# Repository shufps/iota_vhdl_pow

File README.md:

# IOTA VHDL PoW (Pearl Diver)

Project moved to:

https://gitlab.com/microengineer18/pidiver1.3/wikis/home

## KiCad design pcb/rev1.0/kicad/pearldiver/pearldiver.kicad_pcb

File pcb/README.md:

Files not suitable for machine assembly!
Board files are outdated ... New files with many improvements coming #soon

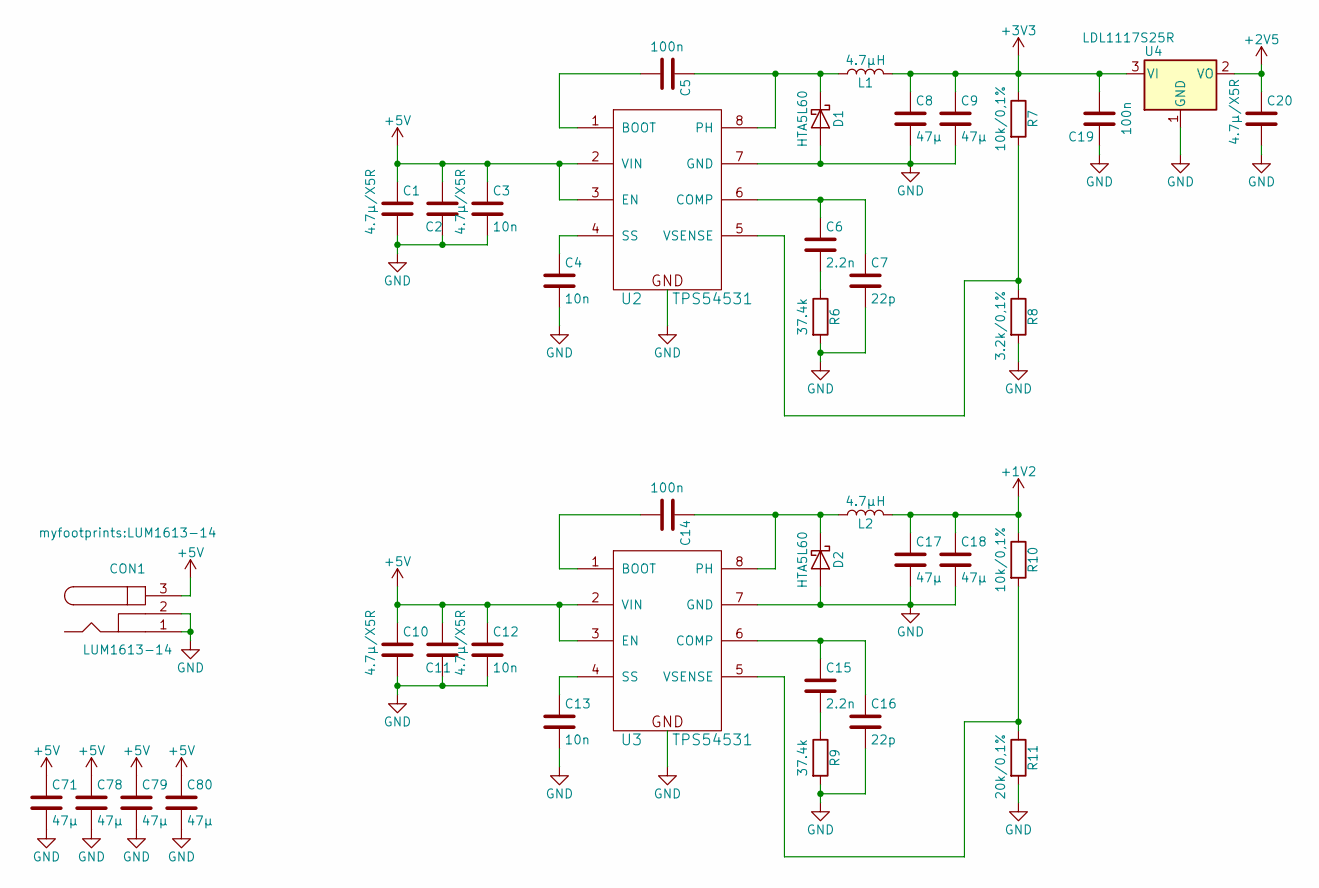
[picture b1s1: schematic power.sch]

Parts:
C1, C2, C10, C11, C20: 4.7µ/X5R; C_1206
C3, C4, C12, C13: 10n; C_0805
C5, C14: 100n; C_0805
C6, C15: 2.2n; C_0805
C7, C16: 22p; C_0603
C8, C9, C17, C18, C71, C78, C79, C80: 47µ; C_1210
C19: 100n; C_1206
CON1: LUM1613-14
D1, D2: HTA5L60; D_SMA
L1, L2: 4.7µH; IHLP-3232DZ-01
R6, R9: 37.4k; R_1206
R7, R10: 10k/0,1%; R_1206
R8: 3.2k/0,1%; R_1206
R11: 20k/0,1%; R_1206
U2, U3: TPS54531; SOIC-8-1EP_3.9x4.9mm_Pitch1.27mm
U4: LDL1117S25R; SOT-223-3_TabPin2

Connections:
+1V2: C17.1, C18.1, L2.2, R10.1; also elsewhere on the board
+2V5: C20.1, U4.2 (VO); also elsewhere on the board
+5V: C1.1, C2.1, C3.1, C10.1, C11.1, C12.1, C71.1, C78.1, C79.1, C80.1, CON1.3, U2.2 (VIN), U2.3 (EN), U3.2 (VIN), U3.3 (EN); also elsewhere on the board
GND: C1.2, C2.2, C3.2, C4.2, C7.2, C8.2, C9.2, C10.2, C11.2, C12.2, C13.2, C16.2, C17.2, C18.2, C19.1, C20.2, C71.2, C78.2, C79.2, C80.2, CON1.1, CON1.2, D1.2 (A), D2.2 (A), R6.2, R8.2, R9.2, R11.2, U2.7 (GND), U2.9 (GND), U3.7 (GND), U3.9 (GND), U4.1 (GND); also elsewhere on the board
unnamed: C4.1, U2.4 (SS)
unnamed: C5.1, D1.1 (K), L1.1, U2.8 (PH)
unnamed: C5.2, U2.1 (BOOT)
unnamed: C6.1, C7.1, U2.6 (COMP)
unnamed: C6.2, R6.1
unnamed: C13.1, U3.4 (SS)
unnamed: C14.1, D2.1 (K), L2.1, U3.8 (PH)
unnamed: C14.2, U3.1 (BOOT)
unnamed: C15.1, C16.1, U3.6 (COMP)
unnamed: C15.2, R9.1
unnamed: R7.2, R8.1, U2.5 (VSENSE)
unnamed: R10.2, R11.1, U3.5 (VSENSE)

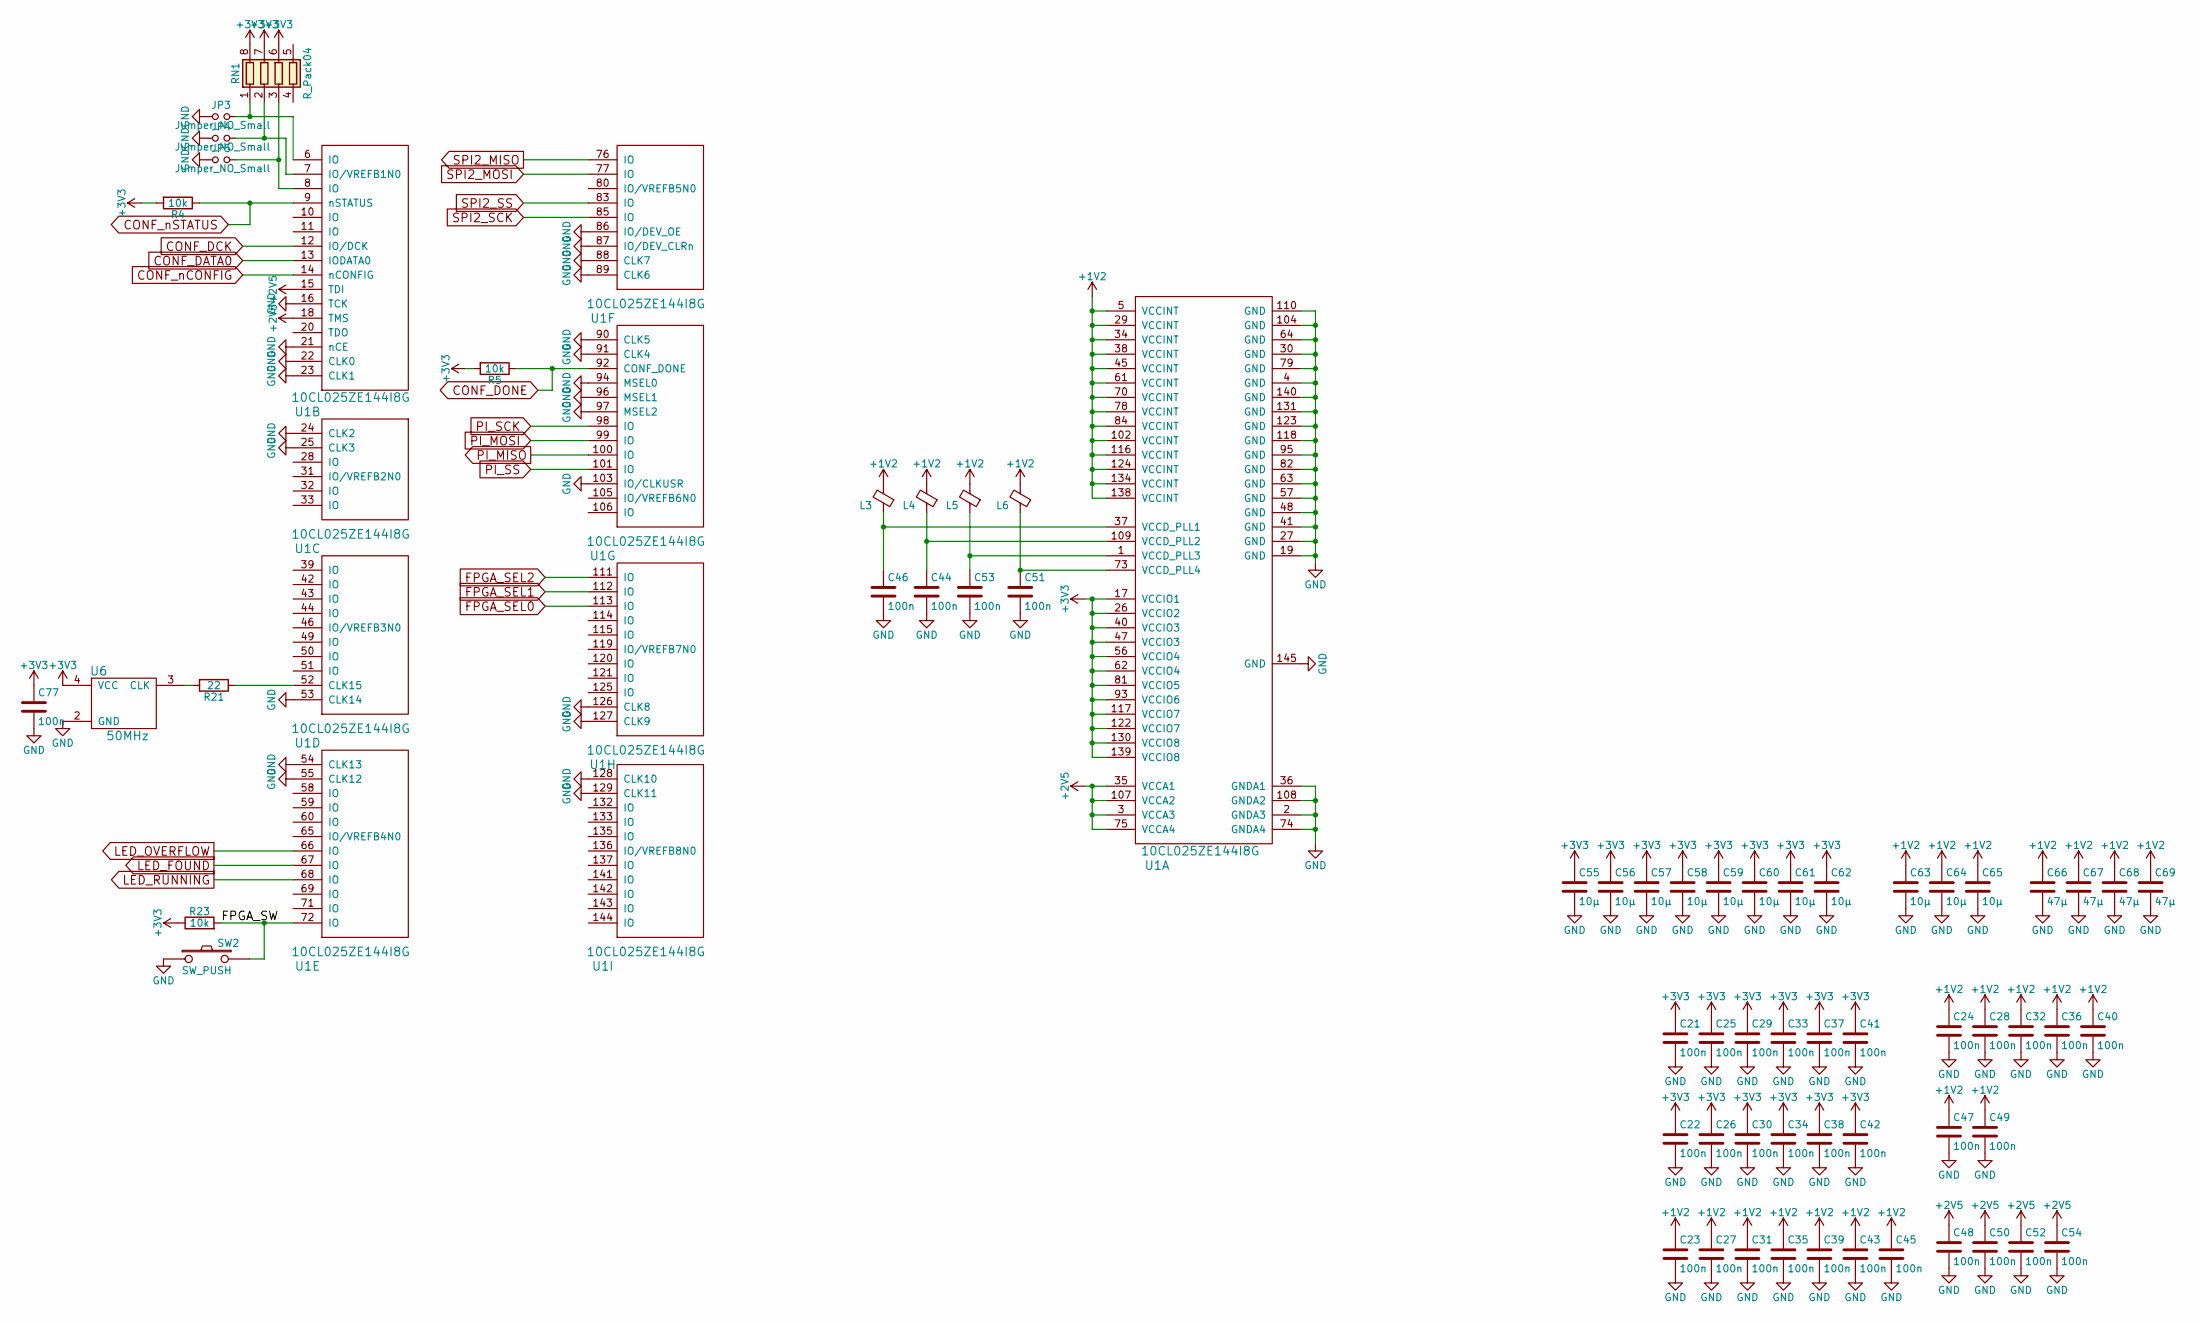
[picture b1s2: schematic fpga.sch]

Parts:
C21, C22, C23, C24, C25, C26, C27, C28, C29, C30, C31, C32, C33, C34, C35, C36, C37, C38, C39, C40, C41, C42, C43, C44, C45, C46, C47, C48, C49, C50, C51, C52, C53, C54: 100n; C_0603
C55, C56, C57, C58, C59, C60, C61, C62, C63, C64, C65: 10µ; C_1206
C66, C67, C68, C69: 47µ; C_1206
C77: 100n; C_0805
JP3, JP4, JP5: Jumper_NO_Small; SOLDERJMP
L3, L4, L5, L6: Ferrite_Bead_Small; R_0805
R4, R5, R23: 10k; R_0805
R21: 22; C_0805
RN1: R_Pack04; R_Array_Convex_4x0603
SW2: SW_PUSH; KURZHUB_SMD
U1: 10CL025ZE144I8G; EQFP-144_20x20mm_Pitch0.5mm
U6: 50MHz; Oscillator_SMD_EuroQuartz_XO32-4pin_3.2x2.5mm_HandSoldering

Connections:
+1V2: C23.1, C24.1, C27.1, C28.1, C31.1, C32.1, C35.1, C36.1, C39.1, C40.1, C43.1, C45.1, C47.1, C49.1, C63.1, C64.1, C65.1, C66.1, C67.1, C68.1, C69.1, L3.2, L4.2, L5.2, L6.2, U1.5 (VCCINT), U1.29 (VCCINT), U1.34 (VCCINT), U1.38 (VCCINT), U1.45 (VCCINT), U1.61 (VCCINT), U1.70 (VCCINT), U1.78 (VCCINT), U1.84 (VCCINT), U1.102 (VCCINT), U1.116 (VCCINT), U1.124 (VCCINT), U1.134 (VCCINT), U1.138 (VCCINT); also elsewhere on the board
+2V5: C48.1, C50.1, C52.1, C54.1, U1.3 (VCCA3), U1.15 (TDI), U1.18 (TMS), U1.35 (VCCA1), U1.75 (VCCA4), U1.107 (VCCA2); also elsewhere on the board
/fpga/FPGA_SW: R23.2, SW2.2, U1.72 (IO)
CONF_DATA0: U1.13 (IODATA0); also elsewhere on the board
CONF_DCK: U1.12 (IO/DCK); also elsewhere on the board
CONF_DONE: R5.1, U1.92 (CONF_DONE); also elsewhere on the board
CONF_nCONFIG: U1.14 (nCONFIG); also elsewhere on the board
CONF_nSTATUS: R4.1, U1.9 (nSTATUS); also elsewhere on the board
FPGA_SEL0: U1.113 (IO); also elsewhere on the board
FPGA_SEL1: U1.112 (IO); also elsewhere on the board
FPGA_SEL2: U1.111 (IO); also elsewhere on the board
GND: C21.2, C22.2, C23.2, C24.2, C25.2, C26.2, C27.2, C28.2, C29.2, C30.2, C31.2, C32.2, C33.2, C34.2, C35.2, C36.2, C37.2, C38.2, C39.2, C40.2, C41.2, C42.2, C43.2, C44.2, C45.2, C46.2, C47.2, C48.2, C49.2, C50.2, C51.2, C52.2, C53.2, C54.2, C55.2, C56.2, C57.2, C58.2, C59.2, C60.2, C61.2, C62.2, C63.2, C64.2, C65.2, C66.2, C67.2, C68.2, C69.2, C77.2, JP3.1, JP4.1, JP5.1, SW2.1, U1.2 (GNDA3), U1.4 (GND), U1.16 (TCK), U1.19 (GND), U1.21 (nCE), U1.22 (CLK0), U1.23 (CLK1), U1.24 (CLK2), U1.25 (CLK3), U1.27 (GND), U1.30 (GND), U1.36 (GNDA1), U1.41 (GND), U1.48 (GND), U1.53 (CLK14), U1.54 (CLK13), U1.55 (CLK12), U1.57 (GND), U1.63 (GND), U1.64 (GND), U1.74 (GNDA4), U1.79 (GND), U1.82 (GND), U1.86 (IO/DEV_OE), U1.87 (IO/DEV_CLRn), U1.88 (CLK7), U1.89 (CLK6), U1.90 (CLK5), U1.91 (CLK4), U1.94 (MSEL0), U1.95 (GND), U1.96 (MSEL1), U1.97 (MSEL2), U1.103 (IO/CLKUSR), U1.104 (GND), U1.108 (GNDA2), U1.110 (GND), U1.118 (GND), U1.123 (GND), U1.126 (CLK8), U1.127 (CLK9), U1.128 (CLK10), U1.129 (CLK11), U1.131 (GND), U1.140 (GND), U1.145 (GND), U6.2 (GND); also elsewhere on the board
LED_FOUND: U1.67 (IO); also elsewhere on the board
LED_OVERFLOW: U1.66 (IO); also elsewhere on the board
LED_RUNNING: U1.68 (IO); also elsewhere on the board
unnamed: C44.1, L4.1, U1.109 (VCCD_PLL2)
unnamed: C46.1, L3.1, U1.37 (VCCD_PLL1)
unnamed: C51.1, L6.1, U1.73 (VCCD_PLL4)
unnamed: C53.1, L5.1, U1.1 (VCCD_PLL3)
unnamed: JP3.2, RN1.1 (R1.1), U1.6 (IO)
unnamed: JP4.2, RN1.2 (R2.1), U1.7 (IO/VREFB1N0)
unnamed: JP5.2, RN1.3 (R3.1), U1.8 (IO)
unnamed: R21.1, U1.52 (CLK15)
unnamed: R21.2, U6.3 (CLK)
PI_MISO: U1.100 (IO); also elsewhere on the board
PI_MOSI: U1.99 (IO); also elsewhere on the board
PI_SCK: U1.98 (IO); also elsewhere on the board
PI_SS: U1.101 (IO); also elsewhere on the board
SPI2_MISO: U1.76 (IO); also elsewhere on the board
SPI2_MOSI: U1.77 (IO); also elsewhere on the board
SPI2_SCK: U1.85 (IO); also elsewhere on the board
SPI2_SS: U1.83 (IO); also elsewhere on the board

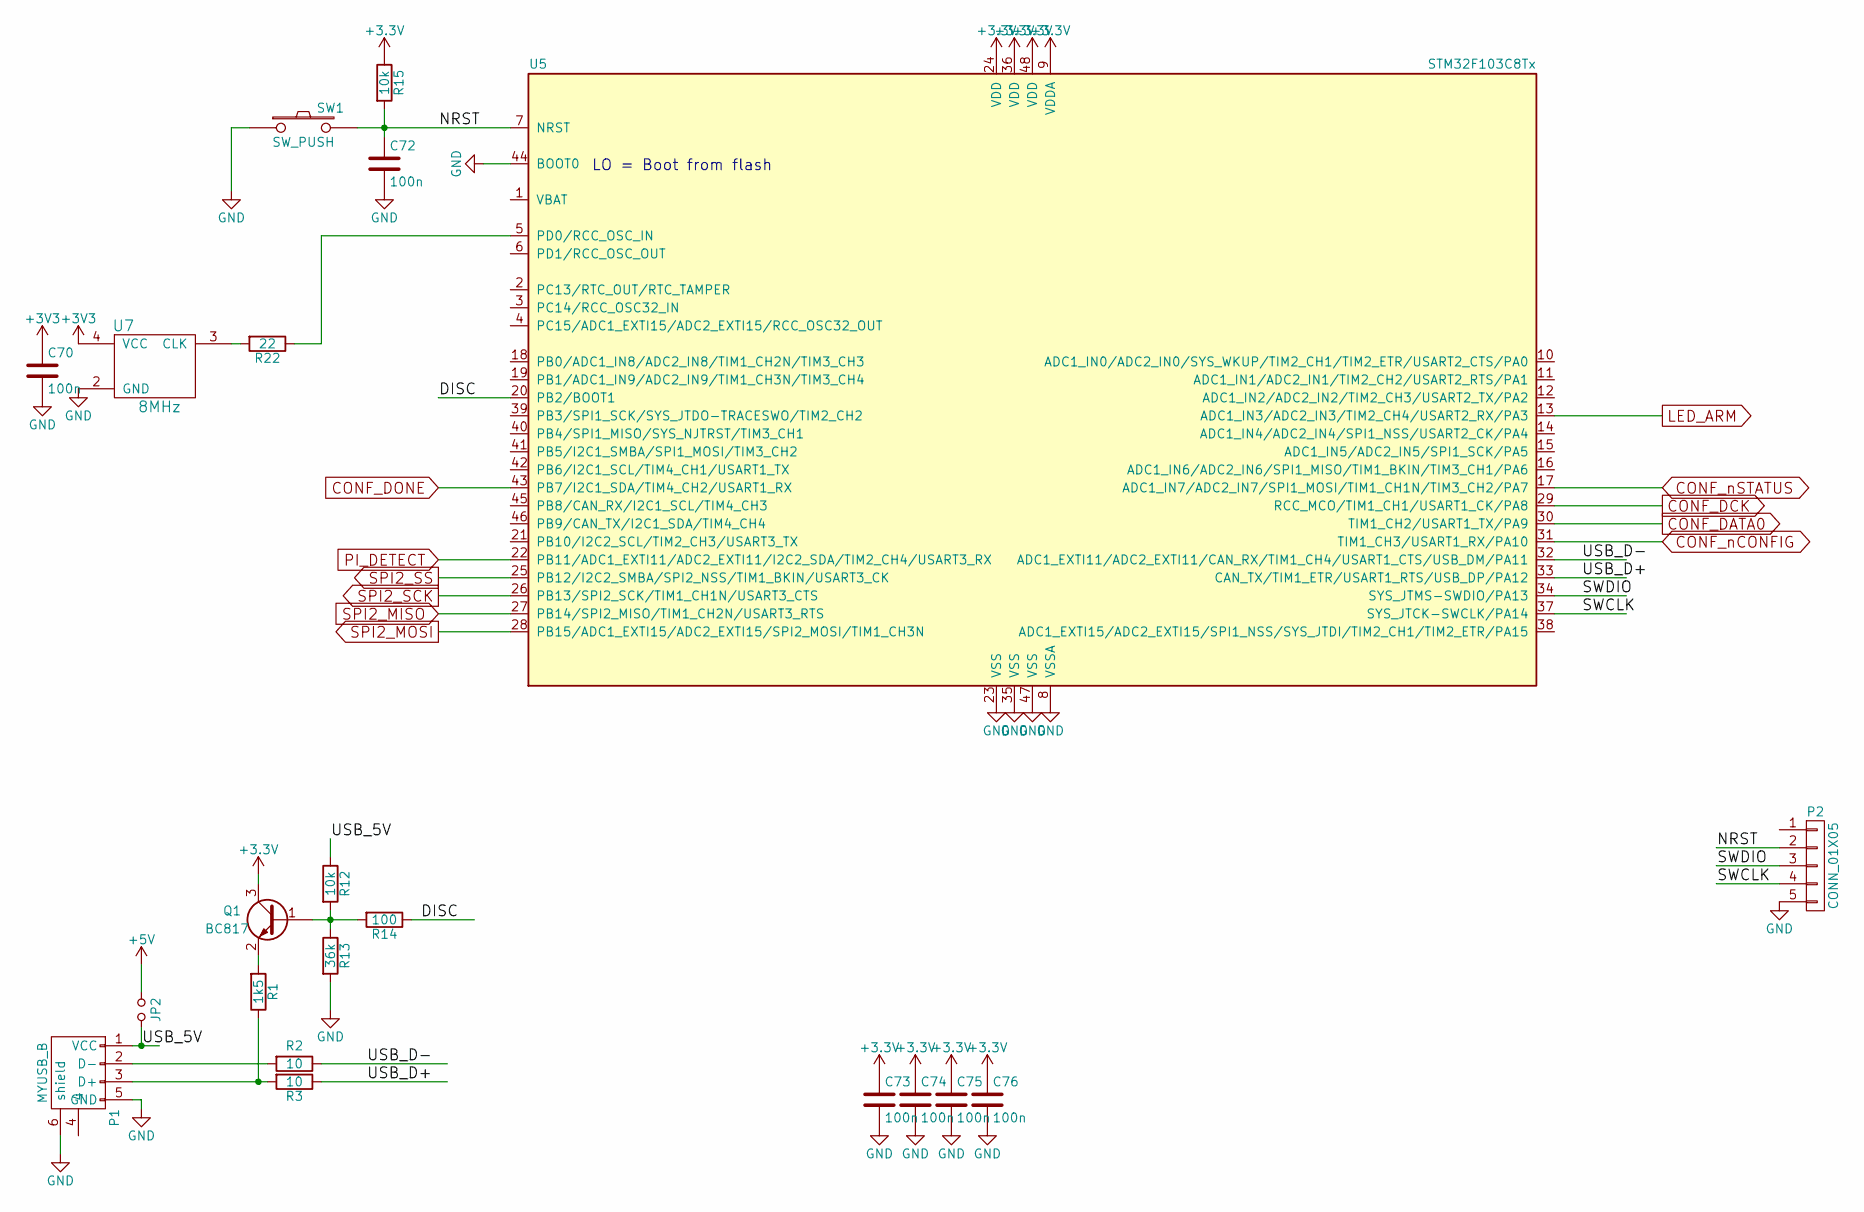
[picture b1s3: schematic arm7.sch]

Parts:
C70, C72, C73, C74, C75, C76: 100n; C_0805
JP2: Jumper_NO_Small; SOLDERJMP
P1: MYUSB_B; MICROUSBB
P2: CONN_01X05; Pin_Header_Straight_1x05_Pitch1.27mm
Q1: BC817; SOT-23
R1: 1k5; R_0805
R2, R3: 10; R_0805
R12, R15: 10k; R_0805
R13: 36k; R_0805
R14: 100; R_0805
R22: 22; C_0805
SW1: SW_PUSH; KURZHUB_SMD
U5: STM32F103C8Tx; LQFP-48_7x7mm_Pitch0.5mm
U7: 8MHz; Oscillator_SMD_EuroQuartz_XO32-4pin_3.2x2.5mm_HandSoldering

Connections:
+5V: JP2.1; also elsewhere on the board
/arm7/DISC: R14.1, U5.20 (PB2/BOOT1)
/arm7/NRST: C72.1, P2.2, R15.2, SW1.2, U5.7 (NRST)
/arm7/SWCLK: P2.4, U5.37 (SYS_JTCK-SWCLK/PA14)
/arm7/SWDIO: P2.3, U5.34 (SYS_JTMS-SWDIO/PA13)
/arm7/USB_5V: JP2.2, P1.1 (VCC), R12.1
/arm7/USB_D+: R3.1, U5.33 (CAN_TX/TIM1_ETR/USART1_RTS/USB_DP/PA12)
/arm7/USB_D-: R2.1, U5.32 (ADC1_EXTI11/ADC2_EXTI11/CAN_RX/TIM1_CH4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)
CONF_DATA0: U5.30 (TIM1_CH2/USART1_TX/PA9); also elsewhere on the board
CONF_DCK: U5.29 (RCC_MCO/TIM1_CH1/USART1_CK/PA8); also elsewhere on the board
CONF_DONE: U5.43 (PB7/I2C1_SDA/TIM4_CH2/USART1_RX); also elsewhere on the board
CONF_nCONFIG: U5.31 (TIM1_CH3/USART1_RX/PA10); also elsewhere on the board
CONF_nSTATUS: U5.17 (ADC1_IN7/ADC2_IN7/SPI1_MOSI/TIM1_CH1N/T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); also elsewhere on the board
GND: C70.2, C72.2, C73.2, C74.2, C75.2, C76.2, P1.5 (GND), P1.6 (shield), P2.5, R13.2, SW1.1, U5.8 (VSSA), U5.23 (VSS), U5.35 (VSS), U5.44 (BOOT0), U5.47 (VSS), U7.2 (GND); also elsewhere on the board
LED_ARM: U5.13 (ADC1_IN3/ADC2_IN3/TIM2_CH4/USART2_RX/PA3); also elsewhere on the board
unnamed: P1.2 (D-), R2.2
unnamed: P1.3 (D+), R1.1, R3.2
unnamed: Q1.1 (B), R12.2, R13.1, R14.2
unnamed: Q1.2 (E), R1.2
unnamed: R22.1, U5.5 (PD0/RCC_OSC_IN)
unnamed: R22.2, U7.3 (CLK)
PI_DETECT: U5.22 (PB11/ADC1_EXTI11/ADC2_EXTI11/I2C2_SDA/T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); also elsewhere on the board
SPI2_MISO: U5.27 (PB14/SPI2_MISO/TIM1_CH2N/USART3_RTS); also elsewhere on the board
SPI2_MOSI: U5.28 (PB15/ADC1_EXTI15/ADC2_EXTI15/SPI2_MOSI/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); also elsewhere on the board
SPI2_SCK: U5.26 (PB13/SPI2_SCK/TIM1_CH1N/USART3_CTS); also elsewhere on the board
SPI2_SS: U5.25 (PB12/I2C2_SMBA/SPI2_NSS/TIM1_BKIN/USART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); also elsewhere on the board

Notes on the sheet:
LO = Boot from flash

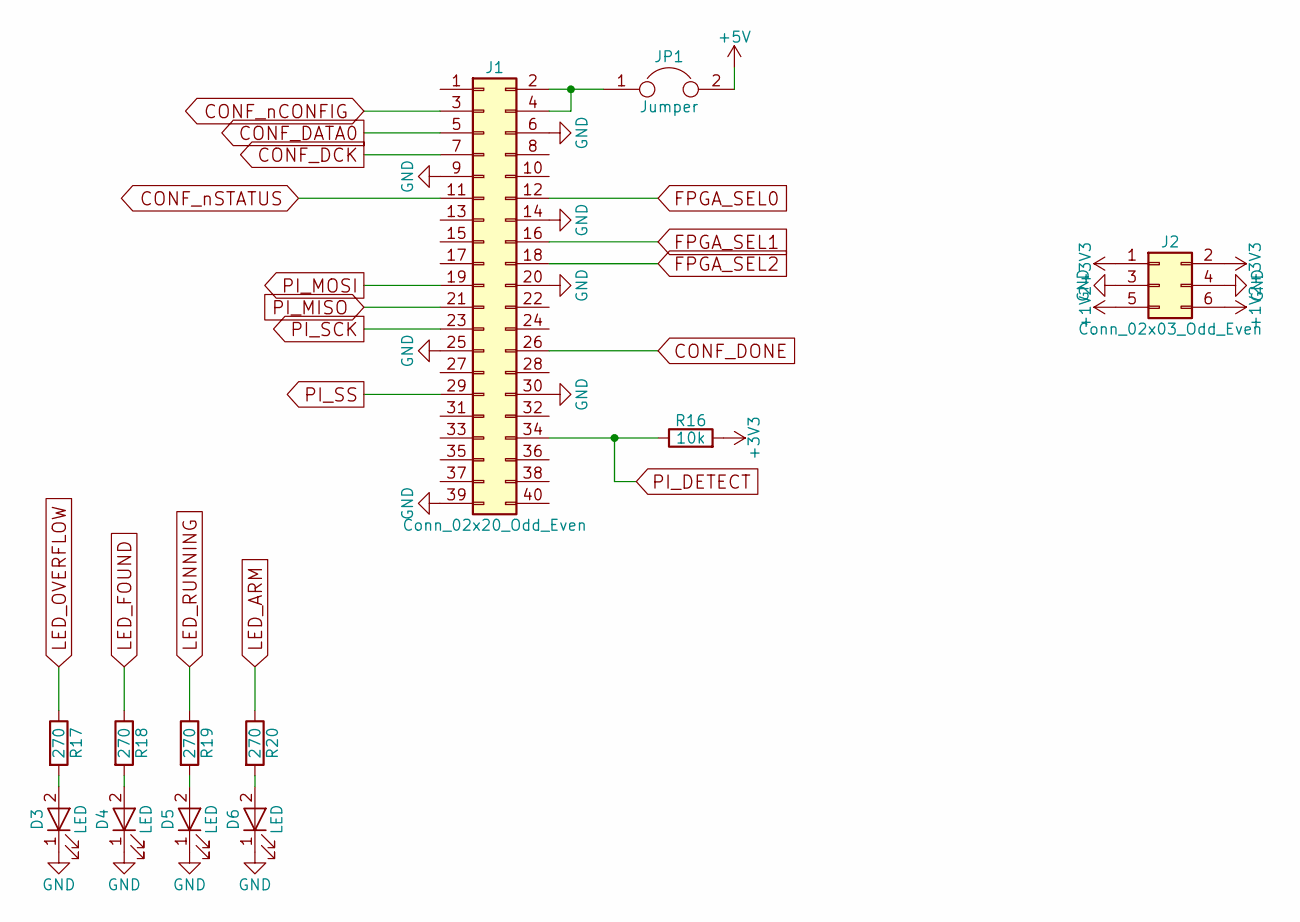
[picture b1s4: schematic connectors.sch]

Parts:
D3, D4, D5, D6: LED; LED_1206
J1: Conn_02x20_Odd_Even; Pin_Header_Straight_2x20_Pitch2.54mm
J2: Conn_02x03_Odd_Even; Pin_Header_Straight_2x03_Pitch2.54mm
JP1: Jumper; SOLDERJMP
R16: 10k; R_0805
R17, R18, R19, R20: 270; R_1206

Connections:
+1V2: J2.5, J2.6; also elsewhere on the board
+5V: JP1.2; also elsewhere on the board
CONF_DATA0: J1.5; also elsewhere on the board
CONF_DCK: J1.7; also elsewhere on the board
CONF_DONE: J1.26; also elsewhere on the board
CONF_nCONFIG: J1.3; also elsewhere on the board
CONF_nSTATUS: J1.11; also elsewhere on the board
FPGA_SEL0: J1.12; also elsewhere on the board
FPGA_SEL1: J1.16; also elsewhere on the board
FPGA_SEL2: J1.18; also elsewhere on the board
GND: D3.1 (K), D4.1 (K), D5.1 (K), D6.1 (K), J1.6, J1.9, J1.14, J1.20, J1.25, J1.30, J1.39, J2.3, J2.4; also elsewhere on the board
LED_ARM: R20.1; also elsewhere on the board
LED_FOUND: R18.1; also elsewhere on the board
LED_OVERFLOW: R17.1; also elsewhere on the board
LED_RUNNING: R19.1; also elsewhere on the board
unnamed: D3.2 (A), R17.2
unnamed: D4.2 (A), R18.2
unnamed: D5.2 (A), R19.2
unnamed: D6.2 (A), R20.2
unnamed: J1.2, J1.4, JP1.1
PI_DETECT: J1.34, R16.1; also elsewhere on the board
PI_MISO: J1.21; also elsewhere on the board
PI_MOSI: J1.19; also elsewhere on the board
PI_SCK: J1.23; also elsewhere on the board
PI_SS: J1.29; also elsewhere on the board

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
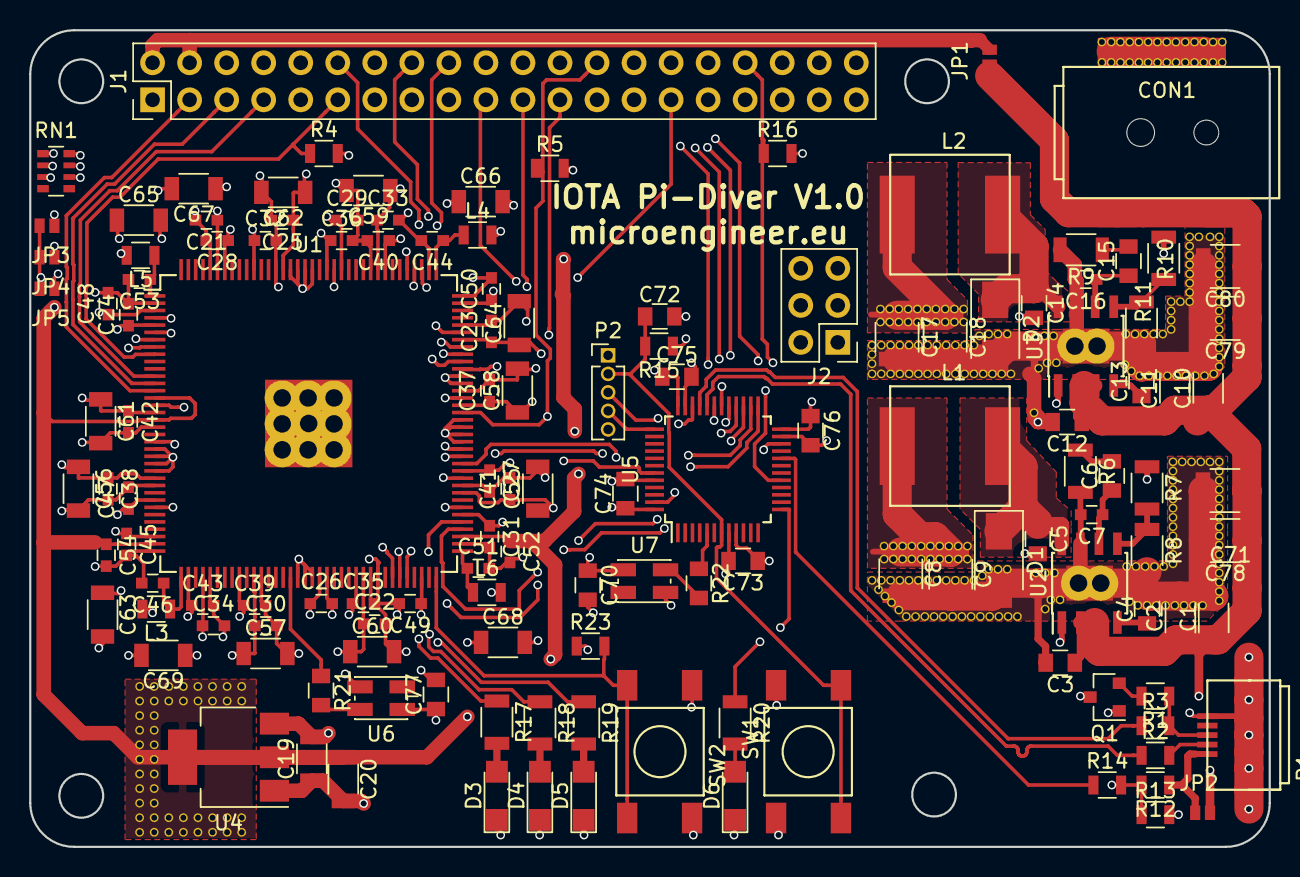
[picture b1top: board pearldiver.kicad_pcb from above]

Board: 4 copper layers, 85.0 x 56.0 mm, 136 parts (0 on the bottom side), 66 nets.

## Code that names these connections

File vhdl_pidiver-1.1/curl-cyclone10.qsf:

# -------------------------------------------------------------------------- #
#
# Copyright (C) 2017  Intel Corporation. All rights reserved.
# Your use of Intel Corporation's design tools, logic functions 
# and other software and tools, and its AMPP partner logic 
# functions, and any output files from any of the foregoing 
# (including device programming or simulation files), and any 
# associated documentation or information are expressly subject 
# to the terms and conditions of the Intel Program License 
# Subscription Agreement, the Intel Quartus Prime License Agreement,
# the Intel FPGA IP License Agreement, or other applicable license
# agreement, including, without limitation, that your use is for
# the sole purpose of programming logic devices manufactured by
# Intel and sold by Intel or its authorized distributors.  Please
# refer to the applicable agreement for further details.
#
# -------------------------------------------------------------------------- #
#
# Quartus Prime
# Version 17.1.0 Build 590 10/25/2017 SJ Lite Edition
# Date created = 10:09:41  April 23, 2018
#
# -------------------------------------------------------------------------- #
#
# Notes:
#
# 1) The default values for assignments are stored in the file:
#		curl-cyclone10_assignment_defaults.qdf
#    If this file doesn't exist, see file:
#		assignment_defaults.qdf
#
# 2) Altera recommends that you do not modify this file. This
#    file is updated automatically by the Quartus Prime software
#    and any changes you make may be lost or overwritten.
#
# -------------------------------------------------------------------------- #


set_global_assignment -name FAMILY "Cyclone 10 LP"
set_global_assignment -name DEVICE 10CL025YE144I7G
set_global_assignment -name TOP_LEVEL_ENTITY de1
set_global_assignment -name ORIGINAL_QUARTUS_VERSION 17.1.0
set_global_assignment -name PROJECT_CREATION_TIME_DATE "10:09:41  APRIL 23, 2018"
set_global_assignment -name LAST_QUARTUS_VERSION "17.1.0 Lite Edition"
set_global_assignment -name PROJECT_OUTPUT_DIRECTORY output_files
set_global_assignment -name MIN_CORE_JUNCTION_TEMP "-40"
set_global_assignment -name MAX_CORE_JUNCTION_TEMP 100
set_global_assignment -name ERROR_CHECK_FREQUENCY_DIVISOR 2
set_global_assignment -name POWER_PRESET_COOLING_SOLUTION "23 MM HEAT SINK WITH 200 LFPM AIRFLOW"
set_global_assignment -name POWER_BOARD_THERMAL_MODEL "NONE (CONSERVATIVE)"
set_location_assignment PIN_52 -to CLOCK_50
set_location_assignment PIN_72 -to reset
set_location_assignment PIN_68 -to led_running
set_location_assignment PIN_66 -to led_overflow
set_location_assignment PIN_67 -to led_found
set_global_assignment -name ENABLE_OCT_DONE OFF
set_global_assignment -name CYCLONEIII_CONFIGURATION_SCHEME "PASSIVE SERIAL"
set_global_assignment -name STRATIXV_CONFIGURATION_SCHEME "PASSIVE SERIAL"
set_global_assignment -name USE_CONFIGURATION_DEVICE OFF
set_global_assignment -name CRC_ERROR_OPEN_DRAIN OFF
set_global_assignment -name OUTPUT_IO_TIMING_NEAR_END_VMEAS "HALF VCCIO" -rise
set_global_assignment -name OUTPUT_IO_TIMING_NEAR_END_VMEAS "HALF VCCIO" -fall
set_global_assignment -name OUTPUT_IO_TIMING_FAR_END_VMEAS "HALF SIGNAL SWING" -rise
set_global_assignment -name OUTPUT_IO_TIMING_FAR_END_VMEAS "HALF SIGNAL SWING" -fall
set_global_assignment -name STRATIX_DEVICE_IO_STANDARD "3.3-V LVCMOS"
set_global_assignment -name CYCLONEII_RESERVE_NCEO_AFTER_CONFIGURATION "USE AS REGULAR IO"
set_global_assignment -name RESERVE_DATA1_AFTER_CONFIGURATION "USE AS REGULAR IO"
set_global_assignment -name RESERVE_FLASH_NCE_AFTER_CONFIGURATION "USE AS REGULAR IO"
set_location_assignment PIN_12 -to ~ALTERA_DCLK~
set_location_assignment PIN_13 -to ~ALTERA_DATA0~
set_global_assignment -name AUTO_SHIFT_REGISTER_RECOGNITION AUTO
set_global_assignment -name ALLOW_ANY_ROM_SIZE_FOR_RECOGNITION ON
set_global_assignment -name ALLOW_ANY_RAM_SIZE_FOR_RECOGNITION ON
set_global_assignment -name ALLOW_ANY_SHIFT_REGISTER_SIZE_FOR_RECOGNITION ON
set_global_assignment -name ALLOW_SHIFT_REGISTER_MERGING_ACROSS_HIERARCHIES ALWAYS
set_global_assignment -name ADV_NETLIST_OPT_SYNTH_WYSIWYG_REMAP ON
set_global_assignment -name REMOVE_REDUNDANT_LOGIC_CELLS OFF
set_global_assignment -name CYCLONEII_OPTIMIZATION_TECHNIQUE SPEED
set_global_assignment -name PARTITION_NETLIST_TYPE SOURCE -section_id Top
set_global_assignment -name PARTITION_FITTER_PRESERVATION_LEVEL PLACEMENT_AND_ROUTING -section_id Top
set_global_assignment -name PARTITION_COLOR 16764057 -section_id Top
set_global_assignment -name SMART_RECOMPILE ON
set_global_assignment -name PHYSICAL_SYNTHESIS_COMBO_LOGIC ON
set_global_assignment -name PHYSICAL_SYNTHESIS_REGISTER_DUPLICATION ON
set_global_assignment -name PHYSICAL_SYNTHESIS_REGISTER_RETIMING ON
set_global_assignment -name ROUTER_LCELL_INSERTION_AND_LOGIC_DUPLICATION ON
set_global_assignment -name ROUTER_TIMING_OPTIMIZATION_LEVEL MAXIMUM
set_global_assignment -name QII_AUTO_PACKED_REGISTERS NORMAL
set_global_assignment -name PHYSICAL_SYNTHESIS_ASYNCHRONOUS_SIGNAL_PIPELINING ON
set_global_assignment -name ROUTER_CLOCKING_TOPOLOGY_ANALYSIS ON
set_global_assignment -name FITTER_EFFORT "STANDARD FIT"
set_global_assignment -name MUX_RESTRUCTURE OFF
set_global_assignment -name STATE_MACHINE_PROCESSING "ONE-HOT"
set_global_assignment -name PHYSICAL_SYNTHESIS_COMBO_LOGIC_FOR_AREA OFF
set_global_assignment -name PHYSICAL_SYNTHESIS_MAP_LOGIC_TO_MEMORY_FOR_AREA OFF
set_global_assignment -name AUTO_RAM_RECOGNITION ON
set_global_assignment -name PLACEMENT_EFFORT_MULTIPLIER 8.0
set_global_assignment -name FITTER_AGGRESSIVE_ROUTABILITY_OPTIMIZATION AUTOMATICALLY
set_global_assignment -name OPTIMIZE_TIMING "NORMAL COMPILATION"
set_global_assignment -name OPTIMIZATION_MODE "HIGH PERFORMANCE EFFORT"
set_global_assignment -name ALLOW_REGISTER_DUPLICATION OFF
set_global_assignment -name OPTIMIZE_POWER_DURING_FITTING OFF
set_global_assignment -name ROUTER_EFFORT_MULTIPLIER 16.0
set_global_assignment -name POWER_USE_INPUT_FILES ON
set_location_assignment PIN_100 -to spi1_miso
set_location_assignment PIN_99 -to spi1_mosi
set_location_assignment PIN_98 -to spi1_sck
set_location_assignment PIN_101 -to spi1_ss
set_location_assignment PIN_76 -to spi2_miso
set_location_assignment PIN_77 -to spi2_mosi
set_location_assignment PIN_85 -to spi2_sck
set_location_assignment PIN_83 -to spi2_ss
set_global_assignment -name VHDL_FILE crc.vhd
set_global_assignment -name SDC_FILE "curl-cyclone10.sdc"
set_global_assignment -name VHDL_FILE spi_slave.vhd
set_global_assignment -name VHDL_FILE de1.vhd
set_global_assignment -name VHDL_FILE index_table.vhd
set_global_assignment -name VHDL_FILE curl.vhd
set_global_assignment -name QIP_FILE pll.qip

set_instance_assignment -name WEAK_PULL_UP_RESISTOR ON -to spi1_ss
set_instance_assignment -name WEAK_PULL_UP_RESISTOR ON -to spi2_ss
set_instance_assignment -name PARTITION_HIERARCHY root_partition -to | -section_id Top

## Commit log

2019-02-22 removed obsolete stuff
